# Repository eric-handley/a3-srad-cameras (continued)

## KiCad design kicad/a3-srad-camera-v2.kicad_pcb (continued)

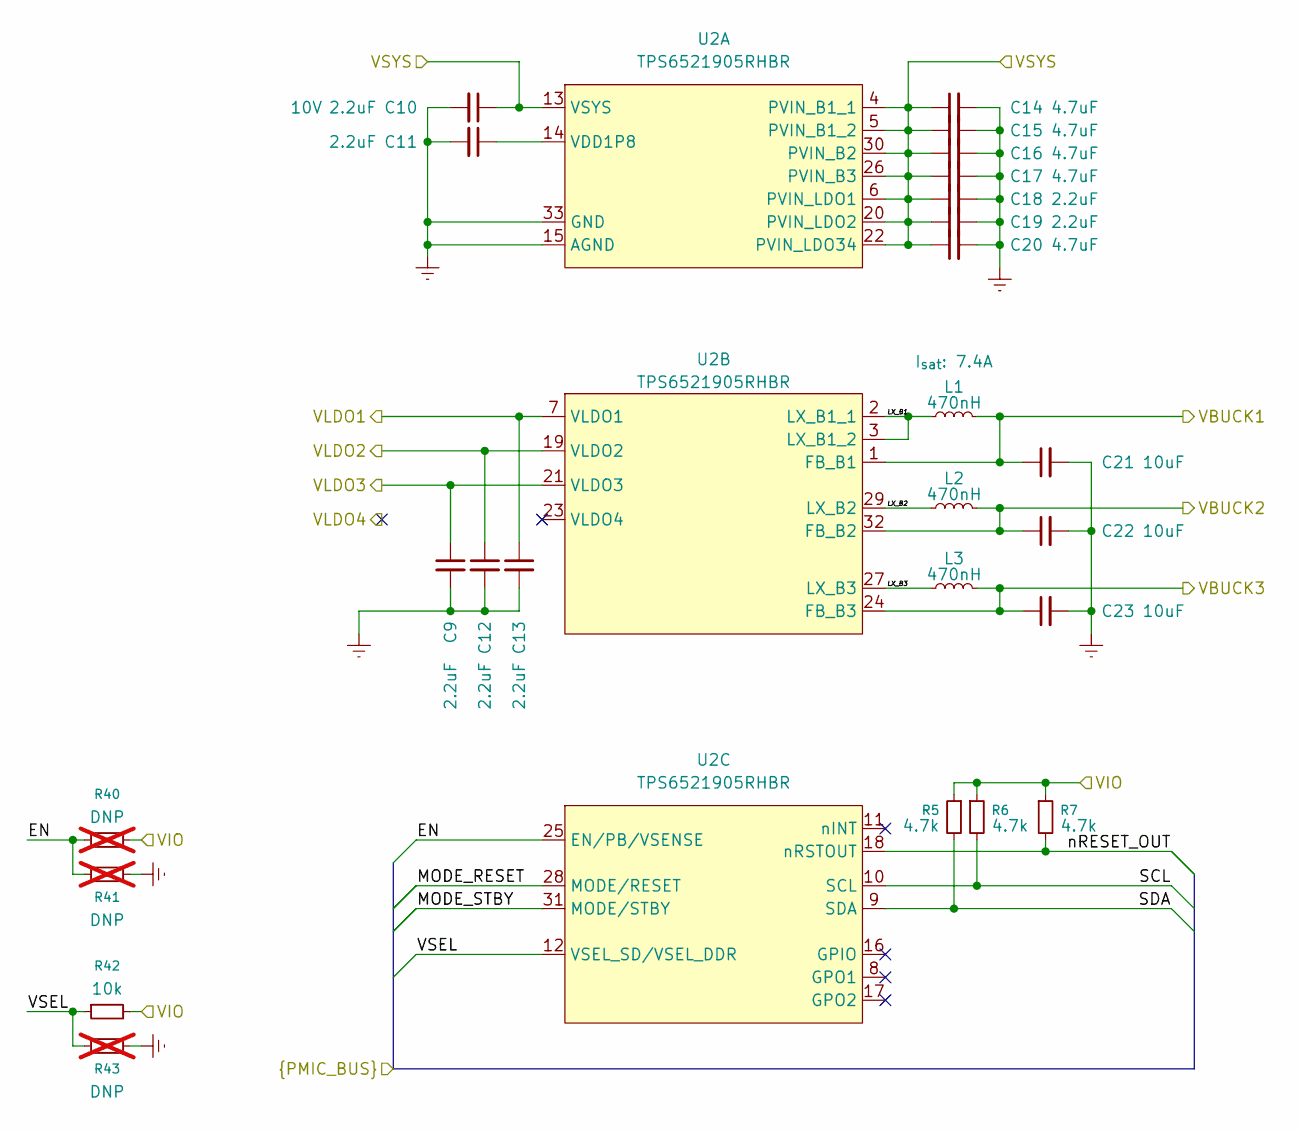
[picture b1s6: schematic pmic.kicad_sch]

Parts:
C9, C11, C12, C13, C18, C19: 2.2uF; C_0805_2012Metric; LCSC PART NAME C15850
C10: 2.2uF; C_0805_2012Metric; DC Rating 10V; LCSC PART NAME C15850
C14, C15, C16, C17, C20: 4.7uF; C_0805_2012Metric; LCSC PART NAME C15850
C21, C22, C23: 10uF; C_0805_2012Metric; LCSC PART NAME C15850
L1, L2, L3: 470nH; L_0806; LCSC PART NAME C89446
R5, R6, R7: 4.7k; R_0402_1005Metric; LCSC PART NAME C2906860
R40, R41, R43: DNP; R_0402_1005Metric; LCSC PART NAME C2906860; not fitted
R42: 10k; R_0402_1005Metric; LCSC PART NAME C2906860
U2: TPS6521905RHBR; TQFN-32_L5.0-W5.0-P0.50-TL-EP3.7; MPN TPS6521905RHBR; LCSC Part C19379192

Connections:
/EN: R40.1, R41.2, U2.25 (EN/PB/VSENSE); also elsewhere on the board
/MODE_RESET: U2.28 (MODE/RESET); also elsewhere on the board
/MODE_STBY: U2.31 (MODE/STBY); also elsewhere on the board
/SCL: R6.2, U2.10 (SCL); also elsewhere on the board
/SDA: R5.2, U2.9 (SDA); also elsewhere on the board
/TPS65219x/LX_B1: L1.1, U2.2 (LX_B1_1), U2.3 (LX_B1_2)
/TPS65219x/LX_B2: L2.1, U2.29 (LX_B2)
/TPS65219x/LX_B3: L3.1, U2.27 (LX_B3)
/VCC_1V8_RK: C9.1, U2.21 (VLDO3); also elsewhere on the board
/VDD_CPU: C22.1, L2.2, U2.32 (FB_B2); also elsewhere on the board
/VDD_DDR: C23.1, L3.2, U2.24 (FB_B3); also elsewhere on the board
/VDD_SOC: C21.1, L1.2, U2.1 (FB_B1); also elsewhere on the board
/VSEL: R42.1, R43.2, U2.12 (VSEL_SD/VSEL_DDR); also elsewhere on the board
/nRESET_OUT: R7.2, U2.18 (nRSTOUT); also elsewhere on the board
GND: C9.2, C10.2, C11.2, C12.2, C13.2, C14.2, C15.2, C16.2, C17.2, C18.2, C19.2, C20.2, C21.2, C22.2, C23.2, R41.1, R43.1, U2.15 (AGND), U2.33 (GND); also elsewhere on the board
unnamed: C11.1, U2.14 (VDD1P8)
VCC_3V3_CAM: C12.1, U2.19 (VLDO2); also elsewhere on the board
VCC_3V3_RK: C13.1, U2.7 (VLDO1); also elsewhere on the board
VIN_5V: C10.1, C14.1, C15.1, C16.1, C17.1, C18.1, C19.1, C20.1, U2.4 (PVIN_B1_1), U2.5 (PVIN_B1_2), U2.6 (PVIN_LDO1), U2.13 (VSYS), U2.20 (PVIN_LDO2), U2.22 (PVIN_LDO34), U2.26 (PVIN_B3), U2.30 (PVIN_B2); also elsewhere on the board
VSYS_3V3: R5.1, R6.1, R7.1, R40.2, R42.2; also elsewhere on the board

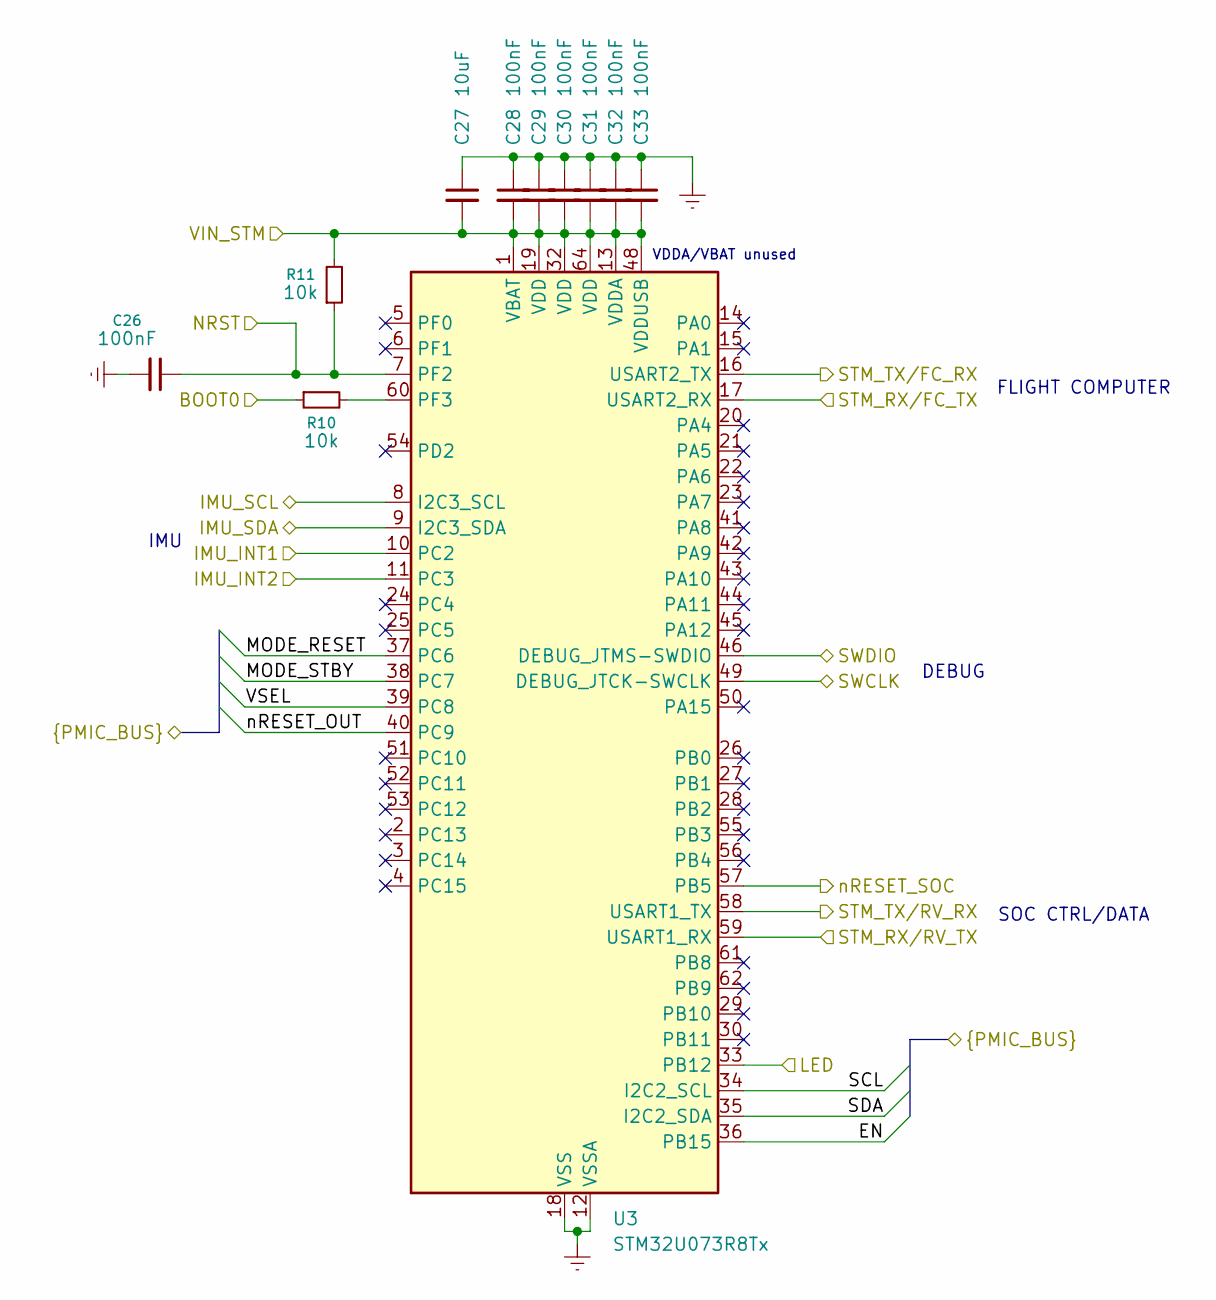
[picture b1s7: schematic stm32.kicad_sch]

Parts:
C26, C28, C29, C30, C31, C32, C33: 100nF; C_0402_1005Metric; LCSC PART NAME C1525
C27: 10uF; C_0805_2012Metric; LCSC PART NAME C15850
R10: 10k; R_0603_1608Metric; LCSC PART NAME C25744
R11: 10k; R_0603_1608Metric; LCSC PART NAME C112291
U3: STM32U073R8Tx; LQFP-64_10x10mm_P0.5mm

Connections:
/EN: U3.36 (PB15); also elsewhere on the board
/IMU_SCL: U3.8 (I2C3_SCL); also elsewhere on the board
/IMU_SDA: U3.9 (I2C3_SDA); also elsewhere on the board
/LSM6DSMTR/INT1: U3.10 (PC2); also elsewhere on the board
/LSM6DSMTR/INT2: U3.11 (PC3); also elsewhere on the board
/MODE_RESET: U3.37 (PC6); also elsewhere on the board
/MODE_STBY: U3.38 (PC7); also elsewhere on the board
/NRST: C26.1, R11.1, U3.7 (PF2); also elsewhere on the board
/SCL: U3.34 (I2C2_SCL); also elsewhere on the board
/SDA: U3.35 (I2C2_SDA); also elsewhere on the board
/STM32U073x/BOOT0: R10.1; also elsewhere on the board
/STM32U073x/LED: U3.33 (PB12); also elsewhere on the board
/STM32U073x/SWCLK: U3.49 (DEBUG_JTCK-SWCLK); also elsewhere on the board
/STM32U073x/SWDIO: U3.46 (DEBUG_JTMS-SWDIO); also elsewhere on the board
/STM_RX/FC_TX: U3.17 (USART2_RX); also elsewhere on the board
/STM_RX/RV_TX: U3.59 (USART1_RX); also elsewhere on the board
/STM_TX/FC_RX: U3.16 (USART2_TX); also elsewhere on the board
/STM_TX/RV_RX: U3.58 (USART1_TX); also elsewhere on the board
/VSEL: U3.39 (PC8); also elsewhere on the board
/nRESET_OUT: U3.40 (PC9); also elsewhere on the board
/nRESET_SOC: U3.57 (PB5); also elsewhere on the board
GND: C26.2, C27.1, C28.1, C29.1, C30.1, C31.1, C32.1, C33.1, U3.12 (VSSA), U3.18 (VSS), U3.31 (VSS), U3.47 (VSS), U3.63 (VSS); also elsewhere on the board
unnamed: R10.2, U3.60 (PF3)
VSYS_3V3: C27.2, C28.2, C29.2, C30.2, C31.2, C32.2, C33.2, R11.2, U3.1 (VBAT), U3.13 (VDDA), U3.19 (VDD), U3.32 (VDD), U3.48 (VDDUSB), U3.64 (VDD); also elsewhere on the board

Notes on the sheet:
VDDA/VBAT unused
IMU
SOC CTRL/DATA
DEBUG
FLIGHT COMPUTER

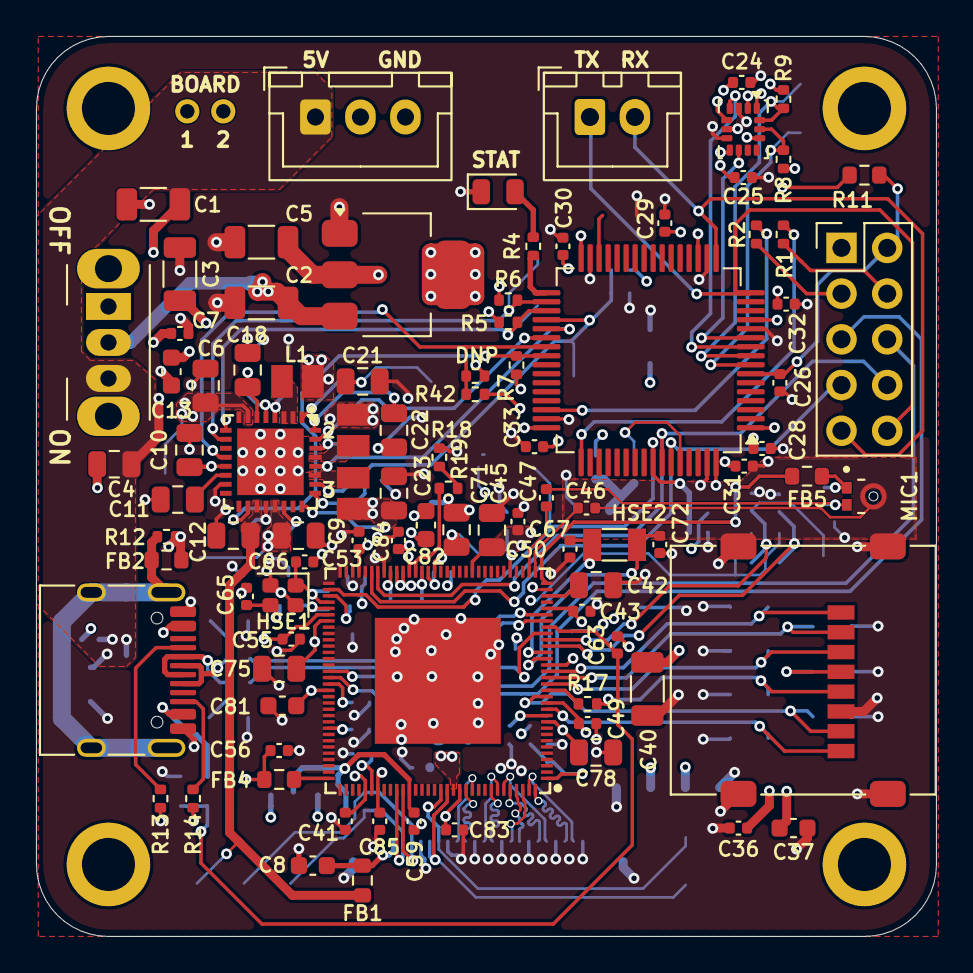
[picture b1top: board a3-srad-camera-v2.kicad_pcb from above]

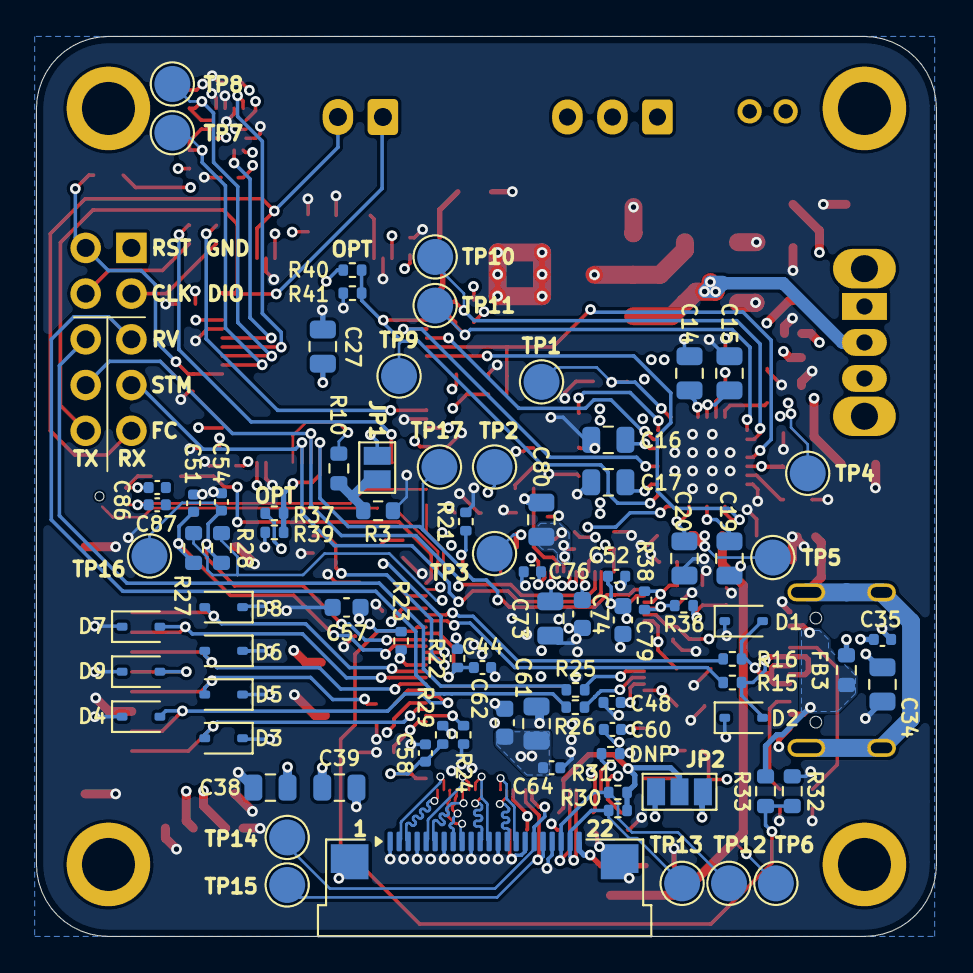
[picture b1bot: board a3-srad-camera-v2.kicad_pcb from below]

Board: 4 copper layers, 50.0 x 50.0 mm, 181 parts (83 on the bottom side), 97 nets.

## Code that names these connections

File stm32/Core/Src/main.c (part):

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  /*Configure GPIO pin Output Level */
  HAL_GPIO_WritePin(GPIOC, GPIO_PIN_6|GPIO_PIN_7|GPIO_PIN_8, GPIO_PIN_RESET);

  /*Configure GPIO pins : PC2 PC3 PC9 */
  GPIO_InitStruct.Pin = GPIO_PIN_2|GPIO_PIN_3|GPIO_PIN_9;
  GPIO_InitStruct.Mode = GPIO_MODE_INPUT;
  GPIO_InitStruct.Pull = GPIO_NOPULL;
  HAL_GPIO_Init(GPIOC, &GPIO_InitStruct);

  /*Configure GPIO pins : PB12 PB15 PB5 */
  GPIO_InitStruct.Pin = GPIO_PIN_12|GPIO_PIN_15|GPIO_PIN_5;
  GPIO_InitStruct.Mode = GPIO_MODE_OUTPUT_PP;
  GPIO_InitStruct.Pull = GPIO_NOPULL;
  GPIO_InitStruct.Speed = GPIO_SPEED_FREQ_LOW;
  HAL_GPIO_Init(GPIOB, &GPIO_InitStruct);

  /*Configure GPIO pins : PC6 PC7 PC8 */
  GPIO_InitStruct.Pin = GPIO_PIN_6|GPIO_PIN_7|GPIO_PIN_8;
  GPIO_InitStruct.Mode = GPIO_MODE_OUTPUT_PP;
  GPIO_InitStruct.Pull = GPIO_NOPULL;
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
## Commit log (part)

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2026-05-23 Update gitignore
2026-05-23 Add docs
2026-05-23 Add almost complete PCB v2
2026-05-24 PCB before switching STM32
2026-05-24 Switch to lower-cost STM32U0
2026-05-24 Init STM32 project for U073C8
2026-05-25 Add missing passives and microphone
2026-05-28 Small changes to PCB, add fab plugin
2026-05-28 Correct PMIC 3d model
2026-05-28 Footprint + silkscreen corrections
2026-06-01 Final changes before order
2026-06-01 Solder paste pattern under QFN chips
2026-06-03 Add IMU driver
2026-06-03 Update toolchain dir
2026-06-03 CMake sources
2026-06-16 Add various docs
2026-06-16 Minor kicad changes
2026-06-16 Update config for STM32U037
2026-06-16 Copy old project files over
2026-06-16 Get debug output working, switch to variadic print function
2026-06-16 Init threads properly
2026-06-16 Status LED thread, IMU debug work
2026-06-16 Basic PMIC driver, confirm chip works
2026-06-20 Finally get PMIC working and outputting all voltages
